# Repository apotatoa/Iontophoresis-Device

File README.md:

# Open Source Iontophoresis Device

## ⚠️ SAFETY WARNING: READ BEFORE BUILDING

> **DANGER:** This project involves the design and construction of a device that applies electrical current to the human body. Improper construction, component failure, or misuse can result in **electric shock, burns, injury, or death**.

* **Galvanic Isolation is mandatory:** Never bypass the isolation barriers designed into this PCB.
* **Battery Power Only:** This device is designed solely for battery operation.
* **Educational Use:** This project is for educational and research purposes only. It is not an FDA-approved medical device.
* **Liability:** The authors and contributors are not responsible for any harm caused by the assembly or use of this device. **Build and use at your own risk.**

---

## Project Overview

This repository contains the complete hardware, firmware, and mechanical design files for a **User-Controlled Iontophoresis Device** intended for the treatment of hyperhidrosis.

The system uses a regulated DC current (typically 0–30mA) applied through water baths to treat excessive sweating of the hands or feet. Unlike simple resistive devices, this project features active closed-loop current regulation, ensuring consistent treatment current regardless of water resistance or skin impedance changes.

To learn more about this project, check out this blog post on maker.io:
> Coming Soon: Link to DigiKey blog post on maker.io

## Key Features

* **Galvanic Isolation:** Physical and electrical separation between the control logic (ESP32) and the high-voltage treatment side using an isolated DC-DC converter (Ag7200) and optocouplers.
* **Active Current Control:** PWM-driven Op-Amp and MOSFET current sink maintains steady current.
* **Automatic Polarity Switching:** Integrated H-Bridge relays automatically reverse polarity halfway through treatment to ensure even effect on both limbs.
* **Safety Fuse:** Hardware-level protection in a quick-blow fuse that physically blocks the current path if it exceeds safety limits (independent of software).

## Repository Structure

```text
Iontophoresis-Device/
├── README.md         # Project documentation and safety warnings
├── 3d/
│   ├── CAD/          # .step files for the enclosure body and lid
│   └── blender/      # .blend files and .mp4 renders for visualization
├── firmware/
│   └── Ionto_Sketch.ino # Arduino source code for the ESP32-S3
└── hardware/
    ├── Ionto.kicad_pro  # KiCad 9.0 Project File
    ├── Ionto.kicad_sch  # Schematic File
    ├── Current_Regulator.kicad_sch    #heirarchal schematic for current regulation 
    ├── H-Bridge.kicad_sch             #heirarchal schematic for H-Bridge
    ├── Ionto.kicad_pcb  # 6-Layer PCB Layout File
    └── jlcpcb/          # Production files (Gerbers, BOM, CPL)
```

## Hardware Design (KiCad)

The PCB is a 6-layer board designed in KiCad 9.0. It utilizes a strict zonal separation layout to maintain safety standards.

* **Dirty Zone (Logic):** ESP32-S3-WROOM-1, USB-C (Programming/Charging), User Controls.
* **Isolation Bridge:** Ag7200 Module (Power) and Optocouplers (Signal).
* **Clean Zone (High Voltage):** Boosted 40V rail, LM358 Op-Amp, IRF540N MOSFET, Relays, and Output Banana Jacks.

### Critical Components
* **MCU:** ESP32-S3 Dev Module
* **Isolation:** Ag7200 (DC-DC), PC817 (Opto)
* **Power:** 11.1V 3S LiPo Battery
* **Current Regulation:** LM358 Op-Amp + IRF540N MOSFET

## Firmware (Arduino/ESP32)

The firmware handles the control loop, user interface, and treatment timing.

### Dependencies
* **Board:** ESP32S3 Dev Module
* **Libraries Required:**
    * `U8g2` (by oliver) - For the OLED Display menu system.
    * `MUIU8g2` - For the menu user interface.
    * `Wire` - Standard I2C library.

### Flashing Instructions
1.  Open `firmware/Ionto_Sketch.ino` in the Arduino IDE.
2.  Install the required libraries via the Library Manager.
3.  Select Board: **ESP32S3 Dev Module**.
4.  Upload to the device.

## Controls

* **Button 1 (Left):** Decrease Value
* **Button 2 (Center):** Increase Value
* **Button 3 (Right):** Enter & Next Field / Start / Stop

## Mechanical (3D & CAD)

The enclosure is designed to be 3D printed.

* **Files:** Located in `3d/CAD/`.
* **Material:** PETG or ABS is recommended for heat resistance and durability, though PLA is sufficient for prototyping.
* **Assembly:** The PCB mounts into the base using M3 screws. The display requires 3x 10.2mm M2 standoff.
* **Note:** Ensure non-conductive washers are used if mounting holes are near copper planes.

## Liability & Disclaimer

This hardware design and software are provided "as is" without warranty of any kind. The user assumes all liability for the assembly, testing, and operation of this device. This device is not certified by any regulatory body (FCC, CE, UL, FDA, etc.).

**By cloning this repository or building this device, you agree that you are solely responsible for your safety and the safety of others.**

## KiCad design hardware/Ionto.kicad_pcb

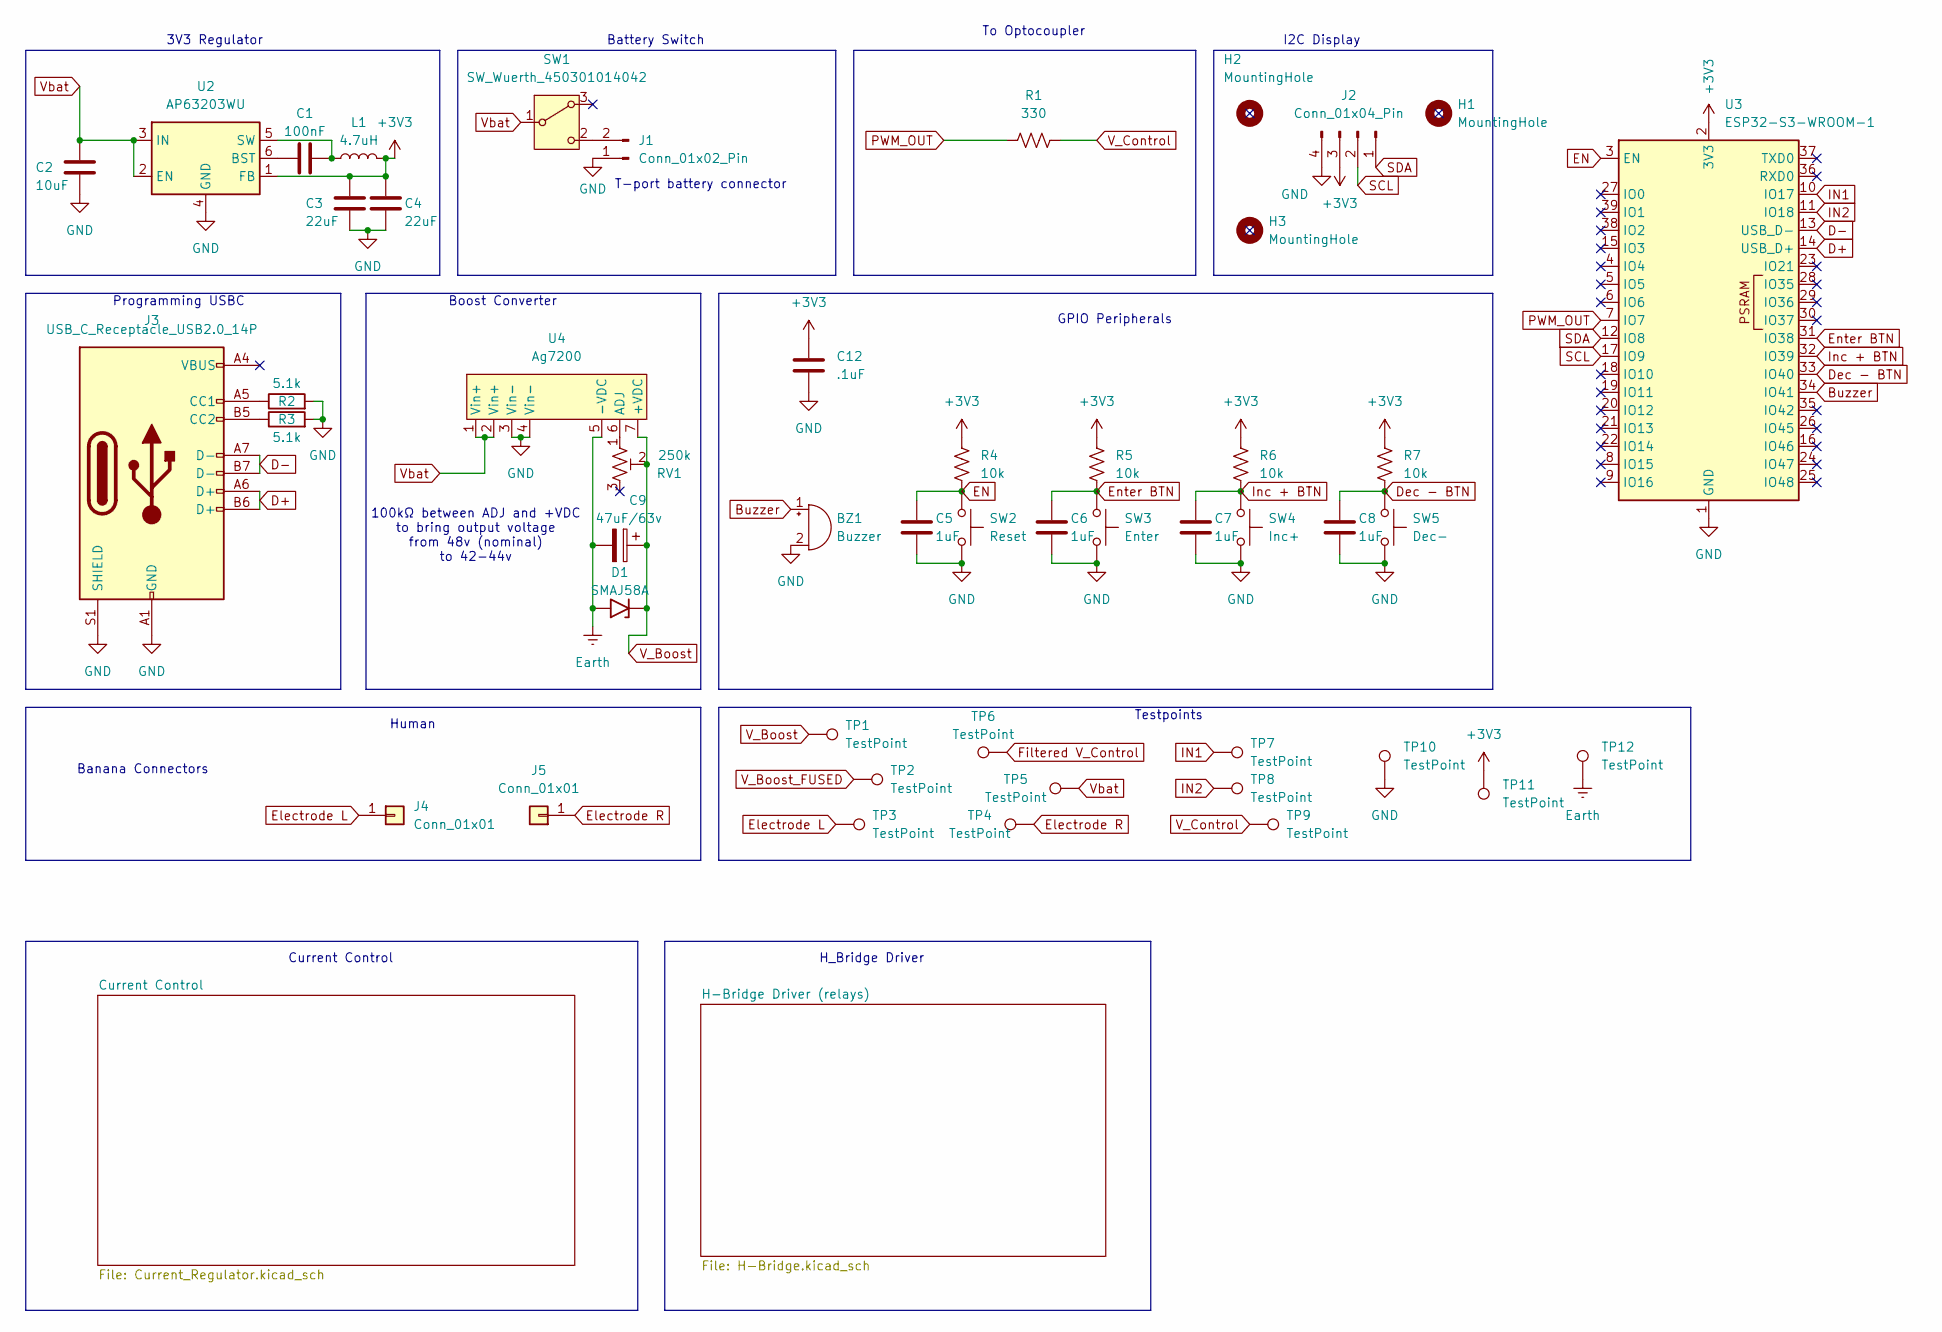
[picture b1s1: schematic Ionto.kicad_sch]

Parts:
BZ1: Buzzer; Buzzer_TDK_PS1240P02BT_D12.2mm_H6.5mm
C1: 100nF; C_0805_2012Metric_Pad1.18x1.45mm_HandSolder
C2: 10uF; C_0805_2012Metric_Pad1.18x1.45mm_HandSolder
C3, C4: 22uF; CP_Elec_5x3
C5, C6, C7, C8: 1uF; C_0805_2012Metric_Pad1.18x1.45mm_HandSolder
C9: 47uF/63v; CP_Elec_8x10
C12: .1uF; C_0805_2012Metric_Pad1.18x1.45mm_HandSolder
D1: SMAJ58A; D_SMA
H1, H2, H3: MountingHole; MountingHole_2.2mm_M2_Pad_TopBottom
J1: Conn_01x02_Pin; TestPoint_2Pads_Pitch5.08mm_Drill1.3mm
J2: Conn_01x04_Pin; PinHeader_1x04_P2.54mm_Vertical
J3: USB_C_Receptacle_USB2.0_14P; USB_C_Receptacle_XKB_U262-16XN-4BVC11
J4: Conn_01x01; Banana_Cliff_FCR7350B_S16N-PC_Horizontal
J5: Conn_01x01; Banana_Cliff_FCR7350R_S16N-PC_Horizontal
L1: 4.7uH; L_7.3x7.3_H4.5
R1: 330; R_0805_2012Metric_Pad1.20x1.40mm_HandSolder
R2, R3: 5.1k; R_0805_2012Metric_Pad1.20x1.40mm_HandSolder
R4, R5, R6, R7: 10k; R_0805_2012Metric_Pad1.20x1.40mm_HandSolder
RV1: 250k; Potentiometer_Bourns_3314G_Vertical
SW1: SW_Wuerth_450301014042; SW_Slide-03_Wuerth-WS-SLTV_10x2.5x6.4_P2.54mm
SW2: Reset; SW_Tactile_SKHH_Angled
SW3: Enter; SW_PUSH-12mm
SW4: Inc+; SW_PUSH-12mm
SW5: Dec-; SW_PUSH-12mm
TP1, TP2, TP3, TP4, TP5, TP6, TP7, TP8, TP9, TP10, TP11, TP12: TestPoint; TestPoint_Pad_D2.0mm
U2: AP63203WU; TSOT-23-6
U3: ESP32-S3-WROOM-1
U4: Ag7200

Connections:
+3V3: C3.1, C4.1, C12.1, J2.3, L1.2, R4.1, R5.1, R6.1, R7.1, TP11.1, U2.1 (FB), U3.2 (3V3)
Buzzer: BZ1.1 (+), U3.34 (IO41)
D+: J3.A6 (D+), J3.B6 (D+), U3.14 (USB_D+)
D-: J3.A7 (D-), J3.B7 (D-), U3.13 (USB_D-)
Dec - BTN: C8.1, R7.2, SW5.1, U3.33 (IO40)
EN: C5.1, R4.2, SW2.1, U3.3 (EN)
Earth: C9.2, D1.2 (A2), TP12.1, U4.5 (-VDC); also elsewhere on the board
Electrode L: J4.1, TP3.1; also elsewhere on the board
Electrode R: J5.1, TP4.1; also elsewhere on the board
Enter BTN: C6.1, R5.2, SW3.1, U3.31 (IO38)
Filtered V_Control: TP6.1; also elsewhere on the board
GND: BZ1.2 (-), C2.2, C3.2, C4.2, C5.2, C6.2, C7.2, C8.2, C12.2, J1.1, J2.4, J3.A1 (GND), J3.A12 (GND), J3.B1 (GND), J3.B12 (GND), J3.S1 (SHIELD), R2.2, R3.2, SW2.2, SW3.2, SW4.2, SW5.2, TP10.1, U2.4 (GND), U3.1 (GND), U3.40 (GND), U3.41 (GND), U4.3 (Vin-), U4.4 (Vin-); also elsewhere on the board
IN1: TP7.1, U3.10 (IO17); also elsewhere on the board
IN2: TP8.1, U3.11 (IO18); also elsewhere on the board
Inc + BTN: C7.1, R6.2, SW4.1, U3.32 (IO39)
unnamed: J1.2, SW1.2 (C)
unnamed: J3.A5 (CC1), R2.1
unnamed: J3.B5 (CC2), R3.1
unnamed: C1.1, U2.6 (BST)
unnamed: C1.2, L1.1, U2.5 (SW)
unnamed: RV1.1, U4.6 (ADJ)
PWM_OUT: R1.1, U3.7 (IO7)
SCL: J2.2, U3.17 (IO9)
SDA: J2.1, U3.12 (IO8)
V_Boost: C9.1, D1.1 (A1), RV1.2, TP1.1, U4.7 (+VDC); also elsewhere on the board
V_Boost_FUSED: TP2.1; also elsewhere on the board
V_Control: R1.2, TP9.1; also elsewhere on the board
Vbat: C2.1, SW1.1 (B), TP5.1, U2.2 (EN), U2.3 (IN), U4.1 (Vin+), U4.2 (Vin+); also elsewhere on the board

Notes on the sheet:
To Optocoupler
3V3 Regulator
Banana Connectors
Testpoints
Programming USBC
Current Control
T-port battery connector
100kΩ between ADJ and +VDC to bring output voltage from 48v (nominal) to 42-44v
H_Bridge Driver
I2C Display
GPIO Peripherals
Battery Switch
Human
Boost Converter

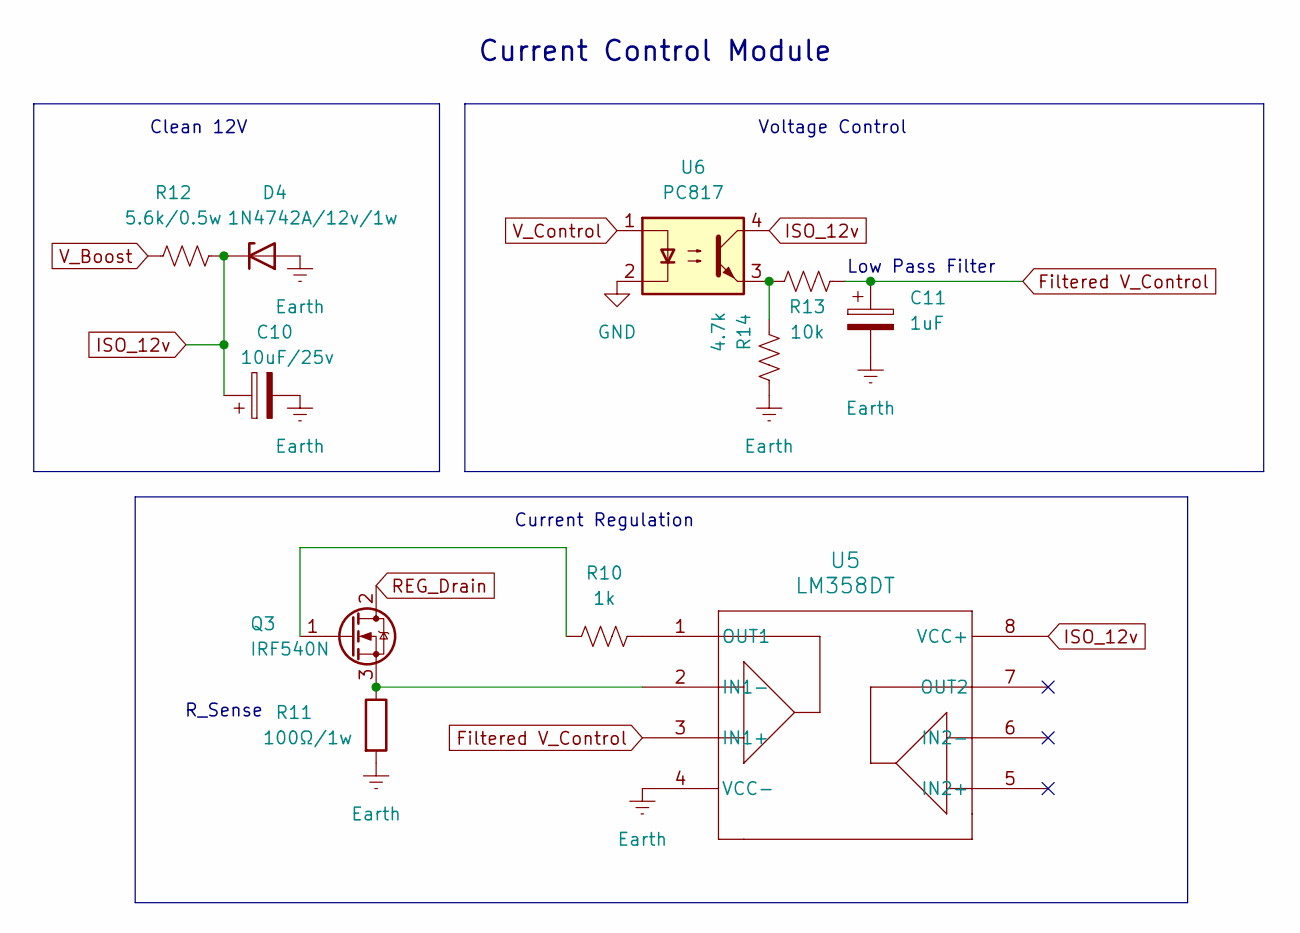
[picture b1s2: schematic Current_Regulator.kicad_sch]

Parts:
C10: 10uF/25v; CP_Elec_8x10
C11: 1uF; C_Elec_5x5.8
D4: 1N4742A/12v/1w; D_DO-41_SOD81_P10.16mm_Horizontal
Q3: IRF540N; TO-220-3_Vertical
R10: 1k; R_0805_2012Metric_Pad1.20x1.40mm_HandSolder
R11: 100Ω/1w; R_Axial_DIN0414_L11.9mm_D4.5mm_P15.24mm_Horizontal
R12: 5.6k/0.5w; R_Axial_DIN0414_L11.9mm_D4.5mm_P15.24mm_Horizontal
R13: 10k; R_0805_2012Metric_Pad1.20x1.40mm_HandSolder
R14: 4.7k; R_0805_2012Metric_Pad1.20x1.40mm_HandSolder
U5: LM358DT; DIP-8_W10.16mm
U6: PC817; DIP-4_W7.62mm

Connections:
Earth: C10.2, C11.2, D4.2 (A), R11.2, R14.1, U5.4 (VCC-); also elsewhere on the board
Filtered V_Control: C11.1, R13.1, U5.3 (IN1+); also elsewhere on the board
GND: U6.2; also elsewhere on the board
ISO_12v: C10.1, D4.1 (K), R12.2, U5.8 (VCC+), U6.4
unnamed: Q3.1 (G), R10.1
unnamed: Q3.3 (S), R11.1, U5.2 (IN1-)
unnamed: R13.2, R14.2, U6.3
unnamed: R10.2, U5.1 (OUT1)
REG_Drain: Q3.2 (D); also elsewhere on the board
V_Boost: R12.1; also elsewhere on the board
V_Control: U6.1; also elsewhere on the board

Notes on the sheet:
Current Regulation
Clean 12V
Current Control Module
Voltage Control
Low Pass Filter
R_Sense

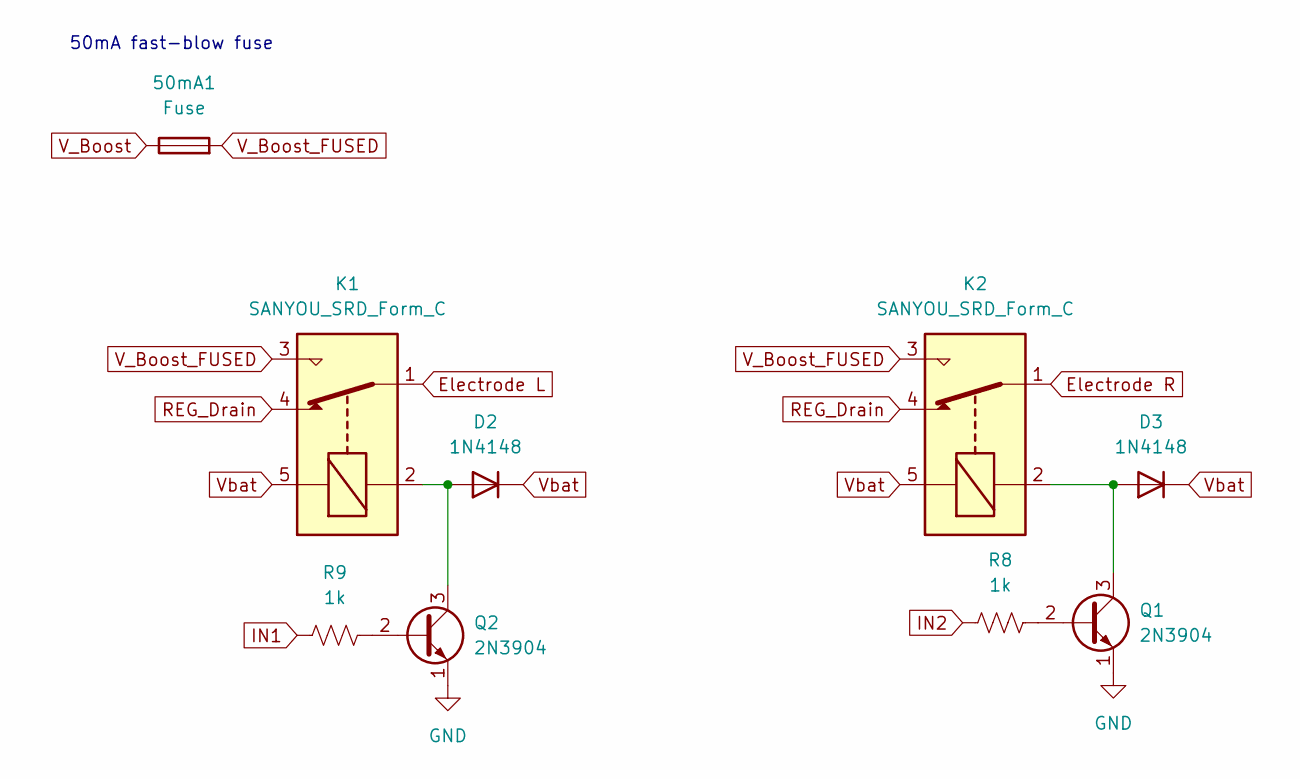
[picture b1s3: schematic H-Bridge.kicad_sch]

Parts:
50mA1: Fuse; Fuse_1206_3216Metric_Pad1.42x1.75mm_HandSolder
D2, D3: 1N4148; D_DO-35_SOD27_P7.62mm_Horizontal
K1, K2: SANYOU_SRD_Form_C; Relay_SPDT_SANYOU_SRD_Series_Form_C
Q1, Q2: 2N3904; TO-92_Inline
R8, R9: 1k; R_0805_2012Metric_Pad1.20x1.40mm_HandSolder

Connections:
Electrode L: K1.1; also elsewhere on the board
Electrode R: K2.1; also elsewhere on the board
GND: Q1.1 (E), Q2.1 (E); also elsewhere on the board
IN1: R9.1; also elsewhere on the board
IN2: R8.1; also elsewhere on the board
unnamed: D2.2 (A), K1.2, Q2.3 (C)
unnamed: D3.2 (A), K2.2, Q1.3 (C)
unnamed: Q1.2 (B), R8.2
unnamed: Q2.2 (B), R9.2
REG_Drain: K1.4, K2.4; also elsewhere on the board
V_Boost: 50mA1.1; also elsewhere on the board
V_Boost_FUSED: 50mA1.2, K1.3, K2.3; also elsewhere on the board
Vbat: D2.1 (K), D3.1 (K), K1.5, K2.5; also elsewhere on the board

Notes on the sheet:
50mA fast-blow fuse

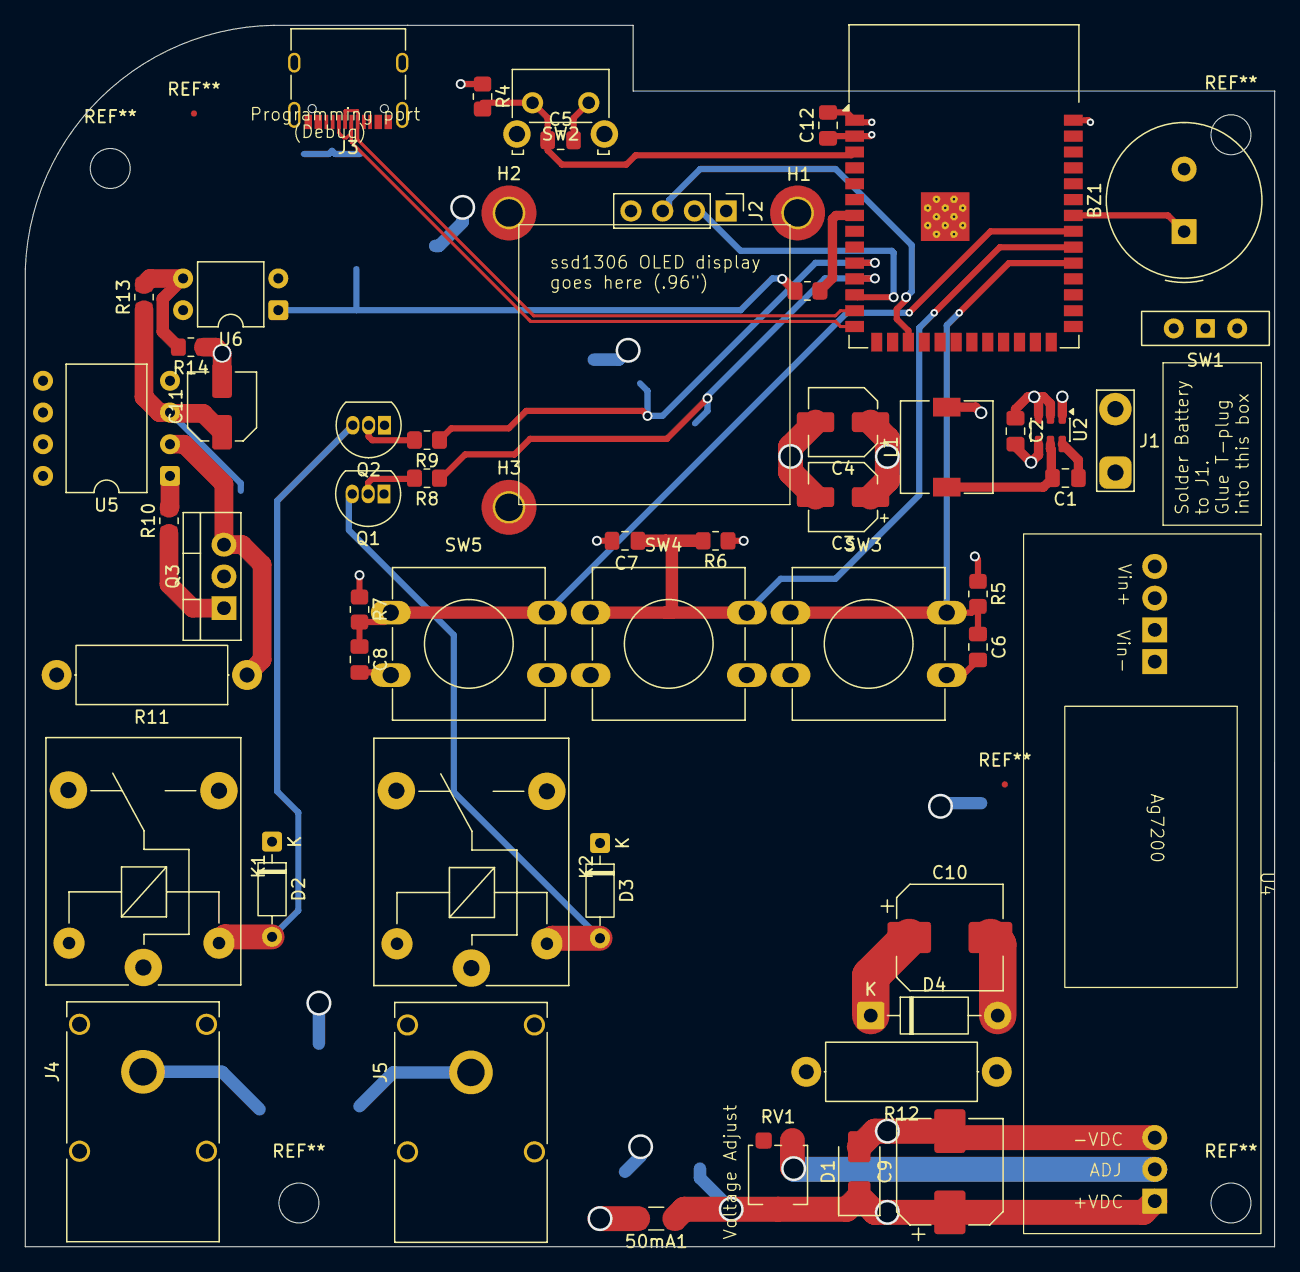
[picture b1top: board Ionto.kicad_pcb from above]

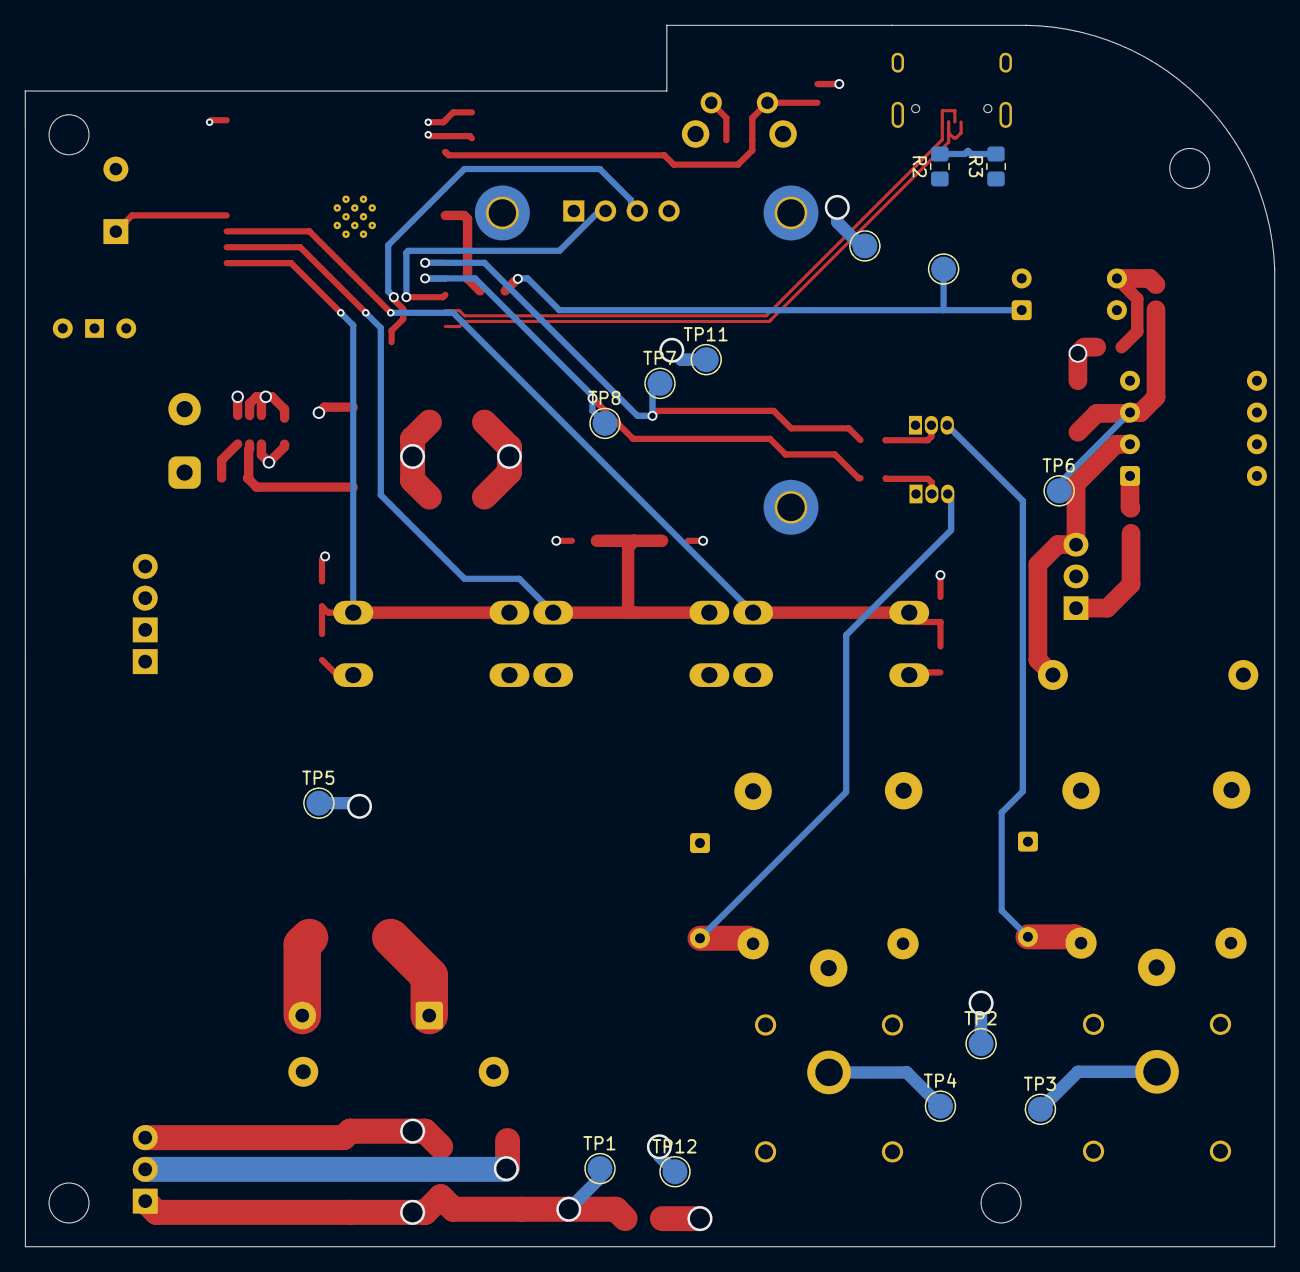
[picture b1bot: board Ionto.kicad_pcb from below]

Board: 6 copper layers, 100.0 x 97.8 mm, 69 parts (14 on the bottom side), 38 nets.

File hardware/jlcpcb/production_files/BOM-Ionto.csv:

Comment,Designator,Footprint,LCSC,Quantity
330,R1,R_0805_2012Metric_Pad1.20x1.40mm_HandSolder,,1
SMAJ58A,D1,D_SMA,,1
10k,R7,R_0805_2012Metric_Pad1.20x1.40mm_HandSolder,,1
100nF,C1,C_0805_2012Metric_Pad1.18x1.45mm_HandSolder,,1
Dec-,SW5,SW_PUSH-12mm,,1
Conn_01x01,J5,Banana_Cliff_FCR7350R_S16N-PC_Horizontal,,1
LM358DT,U5,DIP-8_W10.16mm,,1
Fuse,50mA1,Fuse_1206_3216Metric_Pad1.42x1.75mm_HandSolder,,1
2N3904,Q1,TO-92_Inline,,1
4.7k,R14,R_0805_2012Metric_Pad1.20x1.40mm_HandSolder,,1
10k,R5,R_0805_2012Metric_Pad1.20x1.40mm_HandSolder,,1
Conn_01x02_Pin,J1,TestPoint_2Pads_Pitch5.08mm_Drill1.3mm,,1
1uF,C6,C_0805_2012Metric_Pad1.18x1.45mm_HandSolder,,1
1uF,C11,C_Elec_5x5.8,,1
10uF/25v,C10,CP_Elec_8x10,,1
10k,R6,R_0805_2012Metric_Pad1.20x1.40mm_HandSolder,,1
2N3904,Q2,TO-92_Inline,,1
Inc+,SW4,SW_PUSH-12mm,,1
4.7uH,L1,L_7.3x7.3_H4.5,,1
AP63203WU,U2,TSOT-23-6,,1
.1uF,C12,C_0805_2012Metric_Pad1.18x1.45mm_HandSolder,,1
Conn_01x04_Pin,J2,PinHeader_1x04_P2.54mm_Vertical,,1
22uF,C3,CP_Elec_5x3,,1
10k,R4,R_0805_2012Metric_Pad1.20x1.40mm_HandSolder,,1
Enter,SW3,SW_PUSH-12mm,,1
Reset,SW2,SW_Tactile_SKHH_Angled,,1
1k,R8,R_0805_2012Metric_Pad1.20x1.40mm_HandSolder,,1
IRF540N,Q3,TO-220-3_Vertical,,1
1uF,C8,C_0805_2012Metric_Pad1.18x1.45mm_HandSolder,,1
1uF,C7,C_0805_2012Metric_Pad1.18x1.45mm_HandSolder,,1
SANYOU_SRD_Form_C,K1,Relay_SPDT_SANYOU_SRD_Series_Form_C,,1
47uF/63v,C9,CP_Elec_8x10,,1
250k,RV1,Potentiometer_Bourns_3314G_Vertical,,1
22uF,C4,CP_Elec_5x3,,1
1N4742A/12v/1w,D4,D_DO-41_SOD81_P10.16mm_Horizontal,,1
Buzzer,BZ1,Buzzer_TDK_PS1240P02BT_D12.2mm_H6.5mm,,1
10uF,C2,C_0805_2012Metric_Pad1.18x1.45mm_HandSolder,,1
SANYOU_SRD_Form_C,K2,Relay_SPDT_SANYOU_SRD_Series_Form_C,,1
5.6k/0.5w,R12,R_Axial_DIN0414_L11.9mm_D4.5mm_P15.24mm_Horizontal,,1
1uF,C5,C_0805_2012Metric_Pad1.18x1.45mm_HandSolder,,1
1N4148,D2,D_DO-35_SOD27_P7.62mm_Horizontal,,1
Conn_01x01,J4,Banana_Cliff_FCR7350B_S16N-PC_Horizontal,,1
100Ω/1w,R11,R_Axial_DIN0414_L11.9mm_D4.5mm_P15.24mm_Horizontal,,1
ESP32-S3-WROOM-1,U3,ESP32-S3-WROOM-1,,1
Ag7200,U4,Ag7200,,1
10k,R13,R_0805_2012Metric_Pad1.20x1.40mm_HandSolder,,1
USB_C_Receptacle_USB2.0_14P,J3,USB_C_Receptacle_XKB_U262-16XN-4BVC11,,1
1k,R10,R_0805_2012Metric_Pad1.20x1.40mm_HandSolder,,1
1N4148,D3,D_DO-35_SOD27_P7.62mm_Horizontal,,1
SW_Wuerth_450301014042,SW1,SW_Slide-03_Wuerth-WS-SLTV_10x2.5x6.4_P2.54mm,,1
PC817,U6,DIP-4_W7.62mm,,1
1k,R9,R_0805_2012Metric_Pad1.20x1.40mm_HandSolder,,1
TestPoint,TP4,TestPoint_Pad_D2.0mm,,1
TestPoint,TP2,TestPoint_Pad_D2.0mm,,1
5.1k,R3,R_0805_2012Metric_Pad1.20x1.40mm_HandSolder,,1
TestPoint,TP11,TestPoint_Pad_D2.0mm,,1
5.1k,R2,R_0805_2012Metric_Pad1.20x1.40mm_HandSolder,,1
TestPoint,TP3,TestPoint_Pad_D2.0mm,,1
TestPoint,TP10,TestPoint_Pad_D2.0mm,,1
TestPoint,TP5,TestPoint_Pad_D2.0mm,,1
TestPoint,TP7,TestPoint_Pad_D2.0mm,,1
TestPoint,TP12,TestPoint_Pad_D2.0mm,,1
TestPoint,TP6,TestPoint_Pad_D2.0mm,,1
TestPoint,TP1,TestPoint_Pad_D2.0mm,,1
TestPoint,TP9,TestPoint_Pad_D2.0mm,,1
TestPoint,TP8,TestPoint_Pad_D2.0mm,,1
